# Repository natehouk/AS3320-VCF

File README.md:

# SS-VCF-1
Filter based on the AS3320-VCF.

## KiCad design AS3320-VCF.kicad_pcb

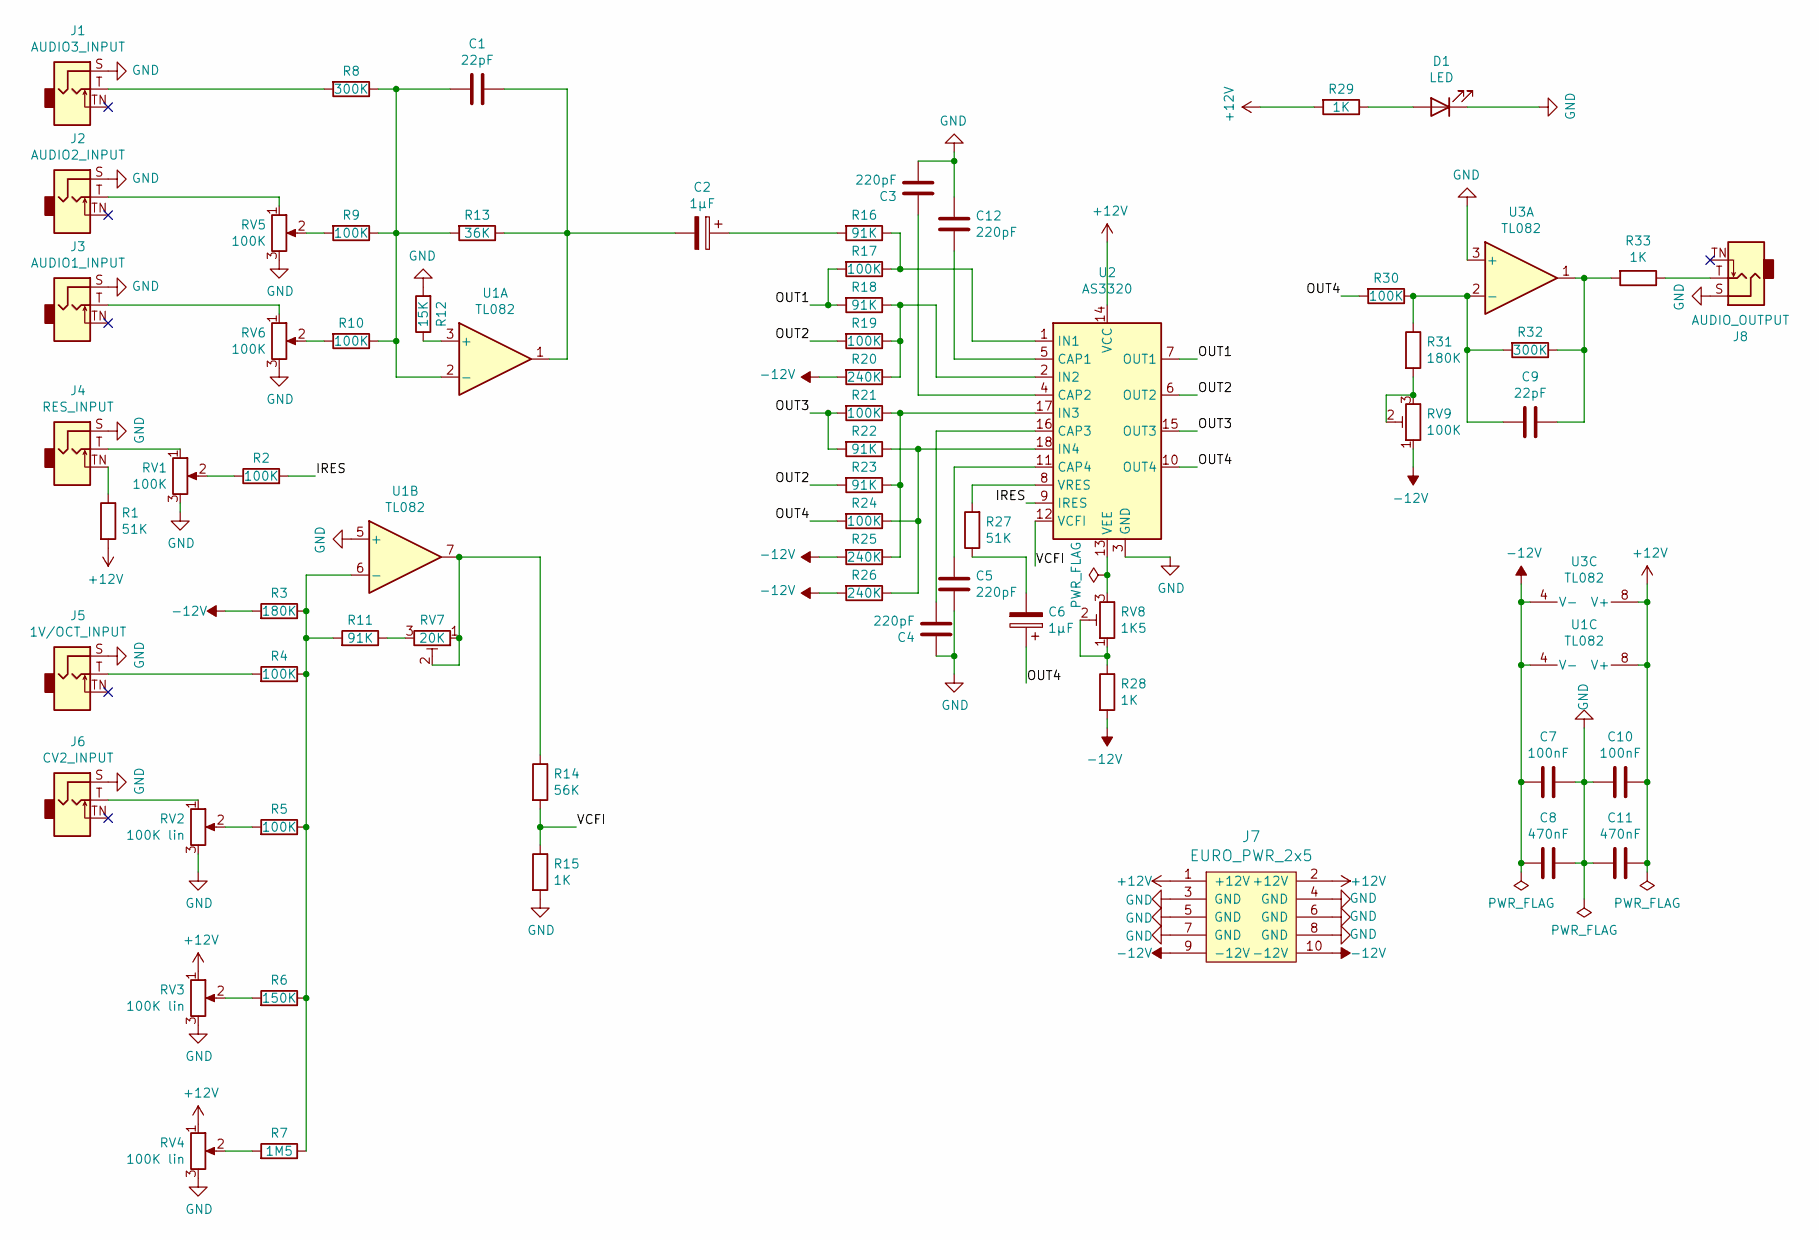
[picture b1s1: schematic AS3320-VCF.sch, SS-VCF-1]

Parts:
C1, C9: 22pF; C_0603_1608Metric
C2, C6: 1µF; CP_Radial_D5.0mm_P2.50mm
C3, C4, C5, C12: 220pF; C_0603_1608Metric
C7, C10: 100nF; C_0603_1608Metric
C8, C11: 470nF; C_0603_1608Metric
D1: LED; D_0603_1608Metric
J1: AUDIO3_INPUT; Jack_3.5mm_QingPu_WQP-PJ398SM_Vertical_CircularHoles
J2: AUDIO2_INPUT; Jack_3.5mm_QingPu_WQP-PJ398SM_Vertical_CircularHoles
J3: AUDIO1_INPUT; Jack_3.5mm_QingPu_WQP-PJ398SM_Vertical_CircularHoles
J4: RES_INPUT; Jack_3.5mm_QingPu_WQP-PJ398SM_Vertical_CircularHoles
J5: 1V/OCT_INPUT; Jack_3.5mm_QingPu_WQP-PJ398SM_Vertical_CircularHoles
J6: CV2_INPUT; Jack_3.5mm_QingPu_WQP-PJ398SM_Vertical_CircularHoles
J7: EURO_PWR_2x5; 3M_2510-6002UB
J8: AUDIO_OUTPUT; Jack_3.5mm_QingPu_WQP-PJ398SM_Vertical_CircularHoles
R1, R27: 51K; R_0603_1608Metric
R2, R4, R5, R9, R10, R17, R19, R21, R24, R30: 100K; R_0603_1608Metric
R3, R31: 180K; R_0603_1608Metric
R6: 150K; R_0603_1608Metric
R7: 1M5; R_0603_1608Metric
R8, R32: 300K; R_0603_1608Metric
R11, R16, R18, R22, R23: 91K; R_0603_1608Metric
R12: 15K; R_0603_1608Metric
R13: 36K; R_0603_1608Metric
R14: 56K; R_0603_1608Metric
R15, R28, R29, R33: 1K; R_0603_1608Metric
R20, R25, R26: 240K; R_0603_1608Metric
RV1, RV5, RV6: 100K; Potentiometer_Alpha_RD901F-40-00D_Single_Vertical
RV2, RV3, RV4: 100K lin; Potentiometer_Alpha_RD901F-40-00D_Single_Vertical
RV7: 20K; TRIM_3266W-1-102LF
RV8: 1K5; TRIM_3266W-1-102LF
RV9: 100K; TRIM_3266W-1-102LF
U1, U3: TL082; DIP-8_W7.62mm_Socket
U2: AS3320; DIP-18_W7.62mm_Socket

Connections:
+12V: C10.1, C11.1, J7.1 (+12V), J7.2 (+12V), R1.2, R29.2, RV3.1, RV4.1, U1.8 (V+), U2.14 (VCC), U3.8 (V+); also elsewhere on the board
-12V: C7.2, C8.2, J7.9 (-12V), J7.10 (-12V), R3.2, R20.2, R25.2, R26.2, R28.2, RV9.1, U1.4 (V-), U3.4 (V-)
/IRES: R2.2, U2.9 (IRES)
/OUT1: R17.2, R18.2, U2.7 (OUT1)
/OUT2: R19.2, R23.2, U2.6 (OUT2)
/OUT3: R21.2, R22.2, U2.15 (OUT3)
/OUT4: C6.1, R24.2, R30.2, U2.10 (OUT4)
/VCFI: R14.2, R15.1, U2.12 (VCFI)
GND: C3.2, C4.1, C5.2, C7.1, C8.1, C10.2, C11.2, C12.1, D1.1 (K), J1.S, J2.S, J3.S, J4.S, J5.S, J6.S, J7.3 (GND), J7.4 (GND), J7.5 (GND), J7.6 (GND), J7.7 (GND), J7.8 (GND), J8.S, R12.2, R15.2, RV1.3, RV2.3, RV3.3, RV4.3, RV5.3, RV6.3, U1.5 (+), U2.3 (GND), U3.3 (+); also elsewhere on the board
unnamed: C1.1, R8.1, R9.1, R10.1, R13.2, U1.2 (-)
unnamed: C1.2, C2.2, R13.1, U1.1
unnamed: C2.1, R16.2
unnamed: C3.1, U2.4 (CAP2)
unnamed: C4.2, U2.16 (CAP3)
unnamed: C5.1, U2.11 (CAP4)
unnamed: C6.2, R27.1
unnamed: C9.1, R32.1, R33.2, U3.1
unnamed: C9.2, R30.1, R31.1, R32.2, U3.2 (-)
unnamed: C12.2, U2.5 (CAP1)
unnamed: D1.2 (A), R29.1
unnamed: J1.T, R8.2
unnamed: J2.T, RV5.1
unnamed: J3.T, RV6.1
unnamed: J4.T, RV1.1
unnamed: J4.TN, R1.1
unnamed: J5.T, R4.2
unnamed: J6.T, RV2.1
unnamed: J8.T, R33.1
unnamed: R2.1, RV1.2
unnamed: R5.2, RV2.2
unnamed 30: R6.2, RV3.2; also elsewhere on the board
unnamed 31: R7.2, RV4.2; also elsewhere on the board
unnamed: R9.2, RV5.2
unnamed: R10.2, RV6.2
unnamed: R11.1, RV7.3
unnamed: R3.1, R4.1, R5.1, R6.1, R7.1, R11.2, U1.6 (-)
unnamed: R12.1, U1.3 (+)
unnamed: R14.1, RV7.1, RV7.2, U1.7
unnamed: R16.1, R17.1, U2.1 (IN1)
unnamed: R18.1, R19.1, R20.1, U2.2 (IN2)
unnamed: R21.1, R23.1, R25.1, U2.17 (IN3)
unnamed: R22.1, R24.1, R26.1, U2.18 (IN4)
unnamed: R27.2, U2.8 (VRES)
unnamed: R28.1, RV8.1, RV8.2
unnamed: R31.2, RV9.2, RV9.3
unnamed: RV8.3, U2.13 (VEE)

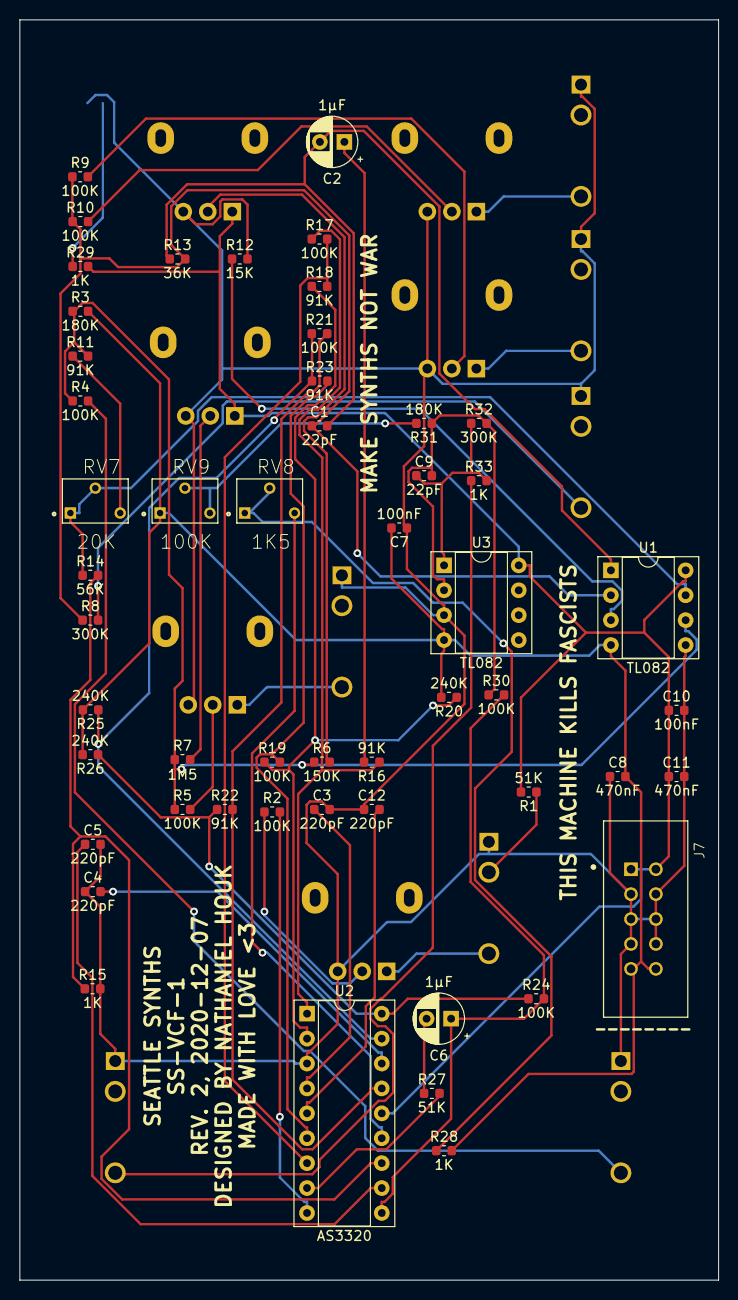
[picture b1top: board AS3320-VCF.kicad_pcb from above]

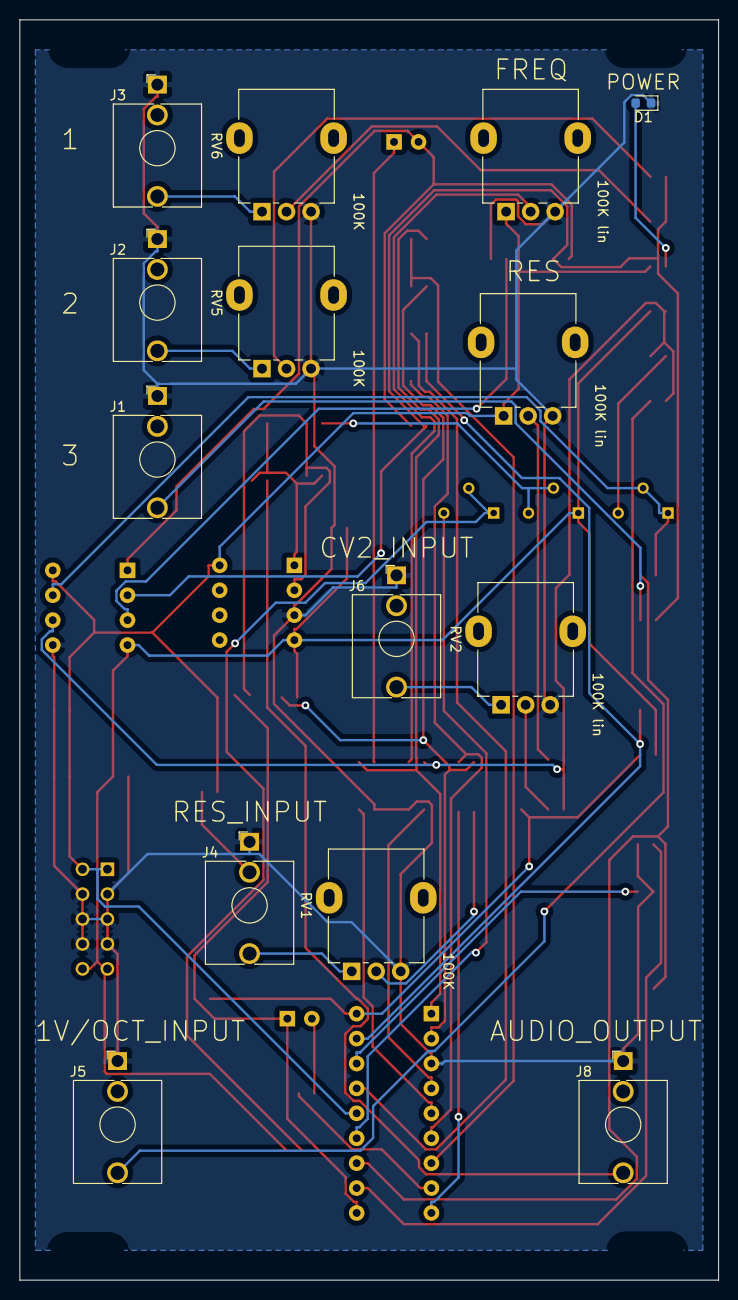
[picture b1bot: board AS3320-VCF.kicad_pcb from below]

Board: 2 copper layers, 71.2 x 128.5 mm, 70 parts (14 on the bottom side), 46 nets.

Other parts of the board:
BOTTOM_LEFT_MOUNT: MountingHole_3.2mm_M3_Oval
BOTTOM_RIGHT_MOUNT: MountingHole_3.2mm_M3_Oval
FREQ: 100K lin; Potentiometer_Alpha_RD901F-40-00D_Single_Vertical
RES: 100K lin; Potentiometer_Alpha_RD901F-40-00D_Single_Vertical
TOP_LEFT_MOUNT: MountingHole_3.2mm_M3_Oval
TOP_RIGHT_MOUNT: MountingHole_3.2mm_M3_Oval

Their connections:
+12V: FREQ.1, RES.1; also elsewhere on the board
GND: FREQ.3, RES.3; also elsewhere on the board
unnamed 30: FREQ.2; also elsewhere on the board
unnamed 31: RES.2; also elsewhere on the board

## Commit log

2020-10-11 Replace board with new footprints for Audio Jacks and Potentiometers
2020-10-11 Replace board with new footprints for Audio Jacks and Potentiometers.
2020-10-11 Generate Gerbers.
2020-10-11 Add BOM.
2020-10-24 Fix ERC errors.
2020-10-24 Refactor to use switched audio jacks.
2020-10-24 Reroute tracks.
2020-10-24 Generate Gerber files.
2020-11-01 Update page settings.
2020-11-02 Fix typo.
2020-11-07 Refactor
2020-12-05 Rev. 1
2020-12-07 Schematic Rev. 2
2020-12-09 Rev2. - Added ground plane, switched to SMD, new layout and rerouted.
2020-12-11 Rev. 2 - Update silk screen text.
2020-12-17 Refactor board
